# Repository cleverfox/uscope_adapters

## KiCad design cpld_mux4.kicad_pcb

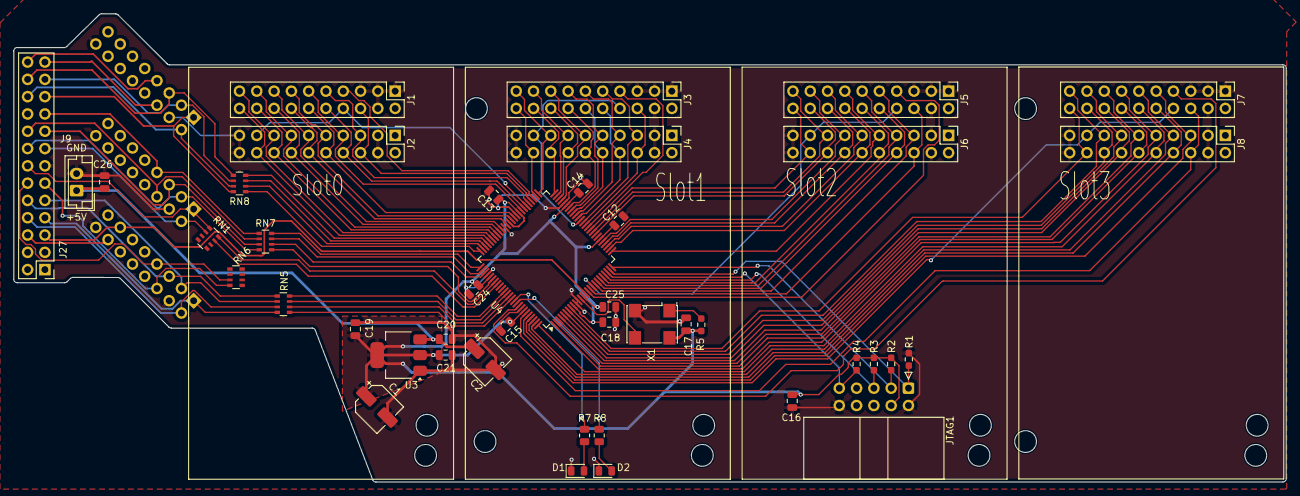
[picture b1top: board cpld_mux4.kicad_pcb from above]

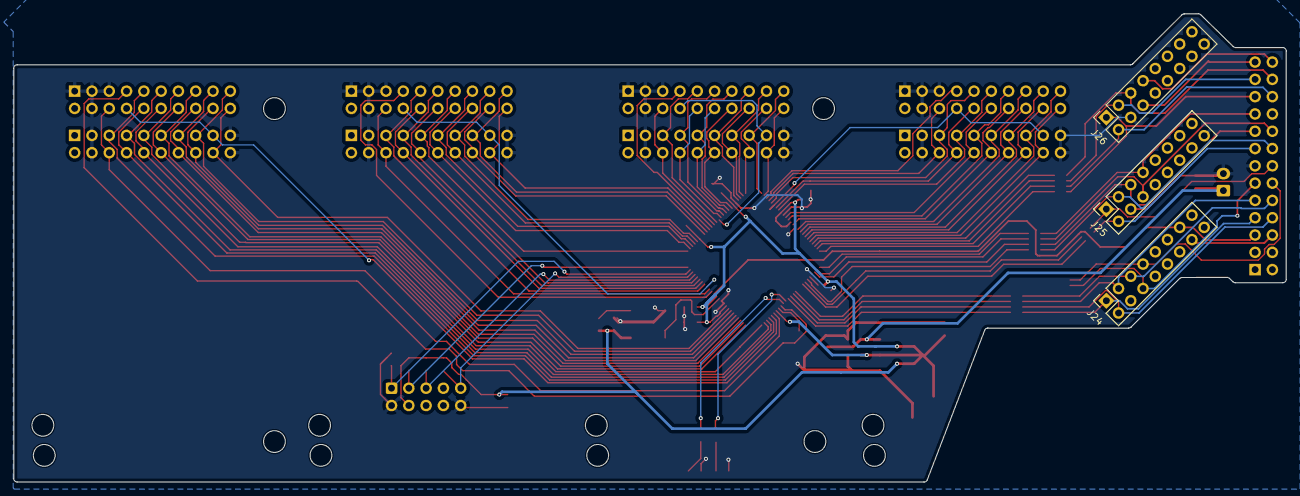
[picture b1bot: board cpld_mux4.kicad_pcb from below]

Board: 2 copper layers, 186.9 x 68.8 mm, 58 parts (3 on the bottom side), 112 nets.

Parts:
C1: 47uF 16V D5xL5.4mm; CP_Elec_5x5.4
C2: 47uF 16V; CP_Elec_5x5.4
C12, C13, C14, C15, C16, C17, C18, C19, C24, C25, C26: 100nF; C_0805_2012Metric
C20, C21: C_Small; C_0805_2012Metric
D1, D2: LED; LED_0805_2012Metric
H1, H3, H5, H7: DAC; MountingHole_3.2mm_M3
H2, H4, H6, H8: ADC; MountingHole_3.2mm_M3
H9, H10, H11, H12: MountingHole; MountingHole_3.2mm_M3
J1, J3, J5, J7: DAC; PinHeader_2x10_P2.54mm_Vertical
J2, J4, J6, J8: ADC; PinHeader_2x10_P2.54mm_Vertical
J9: Conn_01x02_Pin; JST_EH_B2B-EH-A_1x02_P2.50mm_Vertical
J24, J25, J26: Conn_02x08_Odd_Even; PinSocket_2x08_P2.54mm_Vertical
J27: Conn_02x13_Odd_Even; PinHeader_2x13_P2.54mm_Vertical
JTAG1: CONN_02X05; IDC-Header_2x05_P2.54mm_Horizontal
R1, R2, R3, R4: 10K; R_0603_1608Metric_Pad0.98x0.95mm_HandSolder
R5: 0; R_0603_1608Metric_Pad0.98x0.95mm_HandSolder
R7, R8: 1k; R_0805_2012Metric
RN1, RN5, RN6, RN7, RN8: R_Pack04; R_Array_Convex_4x0603
U3: AMS1117-3.3; SOT-223-3_TabPin2
U4: EPM240T100C5N; LQFP-100_14x14mm_P0.5mm
X1: SG-7050CCN; Oscillator_SMD_Abracon_ASV-4Pin_7.0x5.1mm

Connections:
+3V3: C1.1, C12.1, C13.1, C14.1, C15.1, C16.1, C17.1, C18.1, C19.1, C21.1, C24.1, C25.1, JTAG1.4, R2.1, R3.1, R4.1, R5.1, U3.2 (VO), U4.9 (VCCIO1), U4.13 (VCCINT), U4.31 (VCCIO1), U4.45 (VCCIO1), U4.59 (VCCIO2), U4.63 (VCCINT), U4.80 (VCCIO2), U4.94 (VCCIO2), X1.4 (Vdd)
/BA0: RN8.8 (R1.2), U4.72 (IO2_72)
/BA1: RN8.7 (R2.2), U4.73 (IO2_73)
/BA2: RN8.6 (R3.2), U4.74 (IO2_74)
/BA3: RN8.5 (R4.2), U4.75 (IO2_75)
/BA4: RN7.8 (R1.2), U4.76 (IO2_76)
/BA5: RN7.7 (R2.2), U4.77 (IO2_77)
/BA6: RN7.6 (R3.2), U4.78 (IO2_78)
/BA7: RN7.5 (R4.2), U4.81 (IO2_81)
/BA8: RN1.8 (R1.2), U4.82 (IO2_82)
/BA9: RN1.7 (R2.2), U4.83 (IO2_83)
/BA10: RN6.6 (R3.2), U4.84 (IO2_84)
/BA11: RN6.5 (R4.2), U4.85 (IO2_85)
/BA12: RN5.8 (R1.2), U4.86 (IO2_86)
/BA13: RN5.7 (R2.2), U4.87 (IO2_87)
/BA14: RN5.6 (R3.2), U4.88 (IO2_88)
/BA15: RN5.5 (R4.2), U4.89 (IO2_89)
/CM_CLK_M3: J24.13, J27.5, U4.14 (IO1_14/GCLK1)
/CM_STB_N1: J24.14, J27.6
/D1_1: J24.1, J27.7, RN5.4 (R4.1)
/D1_2: J24.2, J27.8, RN5.3 (R3.1)
/D1_3: J24.3, J27.9, RN5.2 (R2.1)
/D1_4: J24.5, J27.10, RN5.1 (R1.1)
/D1_5: J24.6, J27.11, RN6.4 (R4.1)
/D1_6: J24.7, J27.12, RN6.3 (R3.1)
/D2_1: J25.1, J27.14, RN1.1 (R1.1)
/D2_2: J25.2, J27.15, RN1.2 (R2.1)
/D2_3: J25.3, J27.16, RN7.4 (R4.1)
/D2_4: J25.5, J27.17, RN7.3 (R3.1)
/D2_5: J25.6, J27.18, RN7.2 (R2.1)
/D2_6: J25.7, J27.19, RN7.1 (R1.1)
/D3_1: J26.1, J27.21, RN8.4 (R4.1)
/D3_2: J26.2, J27.22, RN8.3 (R3.1)
/D3_3: J26.3, J27.23, RN8.2 (R2.1)
/D3_4: J26.5, J27.24, RN8.1 (R1.1)
/D3_5: J26.6, J27.25
/D3_6: J26.7, J27.26
/LD0: D2.2 (A), R8.2
/LD1: D1.2 (A), R7.2
/LED0: R8.1, U4.91 (IO2_91)
/LED1: R7.1, U4.90 (IO2_90)
/S1D0: J3.20, J4.18, U4.52 (IO2_52)
/S3C: J7.6, J8.6, U4.95 (IO2_95)
/S3D7: J7.13, J8.9, U4.1 (IO2_1)
/S3D8: J7.12, J8.10, U4.100 (IO2_100)
/S3D9: J7.11, J8.7, U4.99 (IO2_99)
/S3D10: J7.10, J8.8, U4.98 (IO2_98)
/S3D11: J7.9, J8.5, U4.97 (IO2_97)
/S3D12: J7.8, J8.17, U4.96 (IO2_96)
/S3D13: J7.7, U4.92 (IO2_92)
/TCK: JTAG1.1, R1.2, U4.24 (TCK)
/TDI: JTAG1.9, R4.2, U4.23 (TDI)
/TDO: JTAG1.3, R2.2, U4.25 (TDO)
/TMS: JTAG1.5, R3.2, U4.22 (TMS)
/VCC_5V: C2.1, C20.1, C26.1, J9.1, U3.3 (VI)
/XTALCLK: U4.12 (IO1_12/GCLK0), X1.3 (OUT)
/ad_da_socket1/CLK: J3.6, J4.6, U4.37 (IO1_37)
/ad_da_socket1/D1: J3.19, J4.15, U4.51 (IO1_51)
/ad_da_socket1/D2: J3.18, J4.16, U4.50 (IO1_50)
/ad_da_socket1/D3: J3.17, J4.13, U4.49 (IO1_49)
/ad_da_socket1/D4: J3.16, J4.14, U4.48 (IO1_48)
/ad_da_socket1/D5: J3.15, J4.11, U4.47 (IO1_47)
/ad_da_socket1/D6: J3.14, J4.12, U4.44 (IO1_44/DEV_CLRn)
/ad_da_socket1/D7: J3.13, J4.9, U4.43 (IO1_43/DEV_OE)
/ad_da_socket1/D8: J3.12, J4.10, U4.42 (IO1_42)
/ad_da_socket1/D9: J3.11, J4.7, U4.41 (IO1_41)
/ad_da_socket1/D10: J3.10, J4.8, U4.40 (IO1_40)
/ad_da_socket1/D11: J3.9, J4.5, U4.38 (IO1_38)
/ad_da_socket1/D12: J3.8, J4.17, U4.39 (IO1_39)
/ad_da_socket1/D13: J3.7, U4.36 (IO1_36)
/ad_da_socket1/VCC_5V: J3.2, J4.1, J4.2
/ad_da_socket2/CLK: J5.6, J6.6, U4.16 (IO1_16)
/ad_da_socket2/D0: J5.20, J6.18, U4.35 (IO1_35)
/ad_da_socket2/D1: J5.19, J6.15, U4.34 (IO1_34)
/ad_da_socket2/D2: J5.18, J6.16, U4.33 (IO1_33)
/ad_da_socket2/D3: J5.17, J6.13, U4.30 (IO1_30)
/ad_da_socket2/D4: J5.16, J6.14, U4.29 (IO1_29)
/ad_da_socket2/D5: J5.15, J6.11, U4.28 (IO1_28)
/ad_da_socket2/D6: J5.14, J6.12, U4.27 (IO1_27)
/ad_da_socket2/D7: J5.13, J6.9, U4.26 (IO1_26)
/ad_da_socket2/D8: J5.12, J6.10, U4.21 (IO1_21)
/ad_da_socket2/D9: J5.11, J6.7, U4.20 (IO1_20)
/ad_da_socket2/D10: J5.10, J6.8, U4.19 (IO1_19)
/ad_da_socket2/D11: J5.9, J6.5, U4.18 (IO1_18)
/ad_da_socket2/D12: J5.8, J6.17, U4.17 (IO1_17)
/ad_da_socket2/D13: J5.7, U4.15 (IO1_15)
/ad_da_socket2/VCC_5V: J5.2, J6.1, J6.2
/ad_da_socket3/D0: J7.20, J8.18, U4.8 (IO1_8)
/ad_da_socket3/D1: J7.19, J8.15, U4.7 (IO1_7)
/ad_da_socket3/D2: J7.18, J8.16, U4.6 (IO1_6)
/ad_da_socket3/D3: J7.17, J8.13, U4.5 (IO1_5)
/ad_da_socket3/D4: J7.16, J8.14, U4.4 (IO1_4)
/ad_da_socket3/D5: J7.15, J8.11, U4.3 (IO1_3)
/ad_da_socket3/D6: J7.14, J8.12, U4.2 (IO1_2)
/ad_da_socket3/VCC_5V: J7.2, J8.1, J8.2
/ad_da_socket/CLK: J1.6, J2.6, U4.54 (IO2_54)
/ad_da_socket/D0: J1.20, J2.18, U4.71 (IO2_71)
/ad_da_socket/D1: J1.19, J2.15, U4.70 (IO2_70)
/ad_da_socket/D2: J1.18, J2.16, U4.69 (IO2_69)
/ad_da_socket/D3: J1.17, J2.13, U4.68 (IO2_68)
/ad_da_socket/D4: J1.16, J2.14, U4.67 (IO2_67)
/ad_da_socket/D5: J1.15, J2.11, U4.66 (IO2_66)
/ad_da_socket/D6: J1.14, J2.12, U4.64 (IO2_64/GCLK3)
/ad_da_socket/D7: J1.13, J2.9, U4.62 (IO2_62/GCLK2)
/ad_da_socket/D8: J1.12, J2.10, U4.61 (IO2_61)
/ad_da_socket/D9: J1.11, J2.7, U4.58 (IO2_58)
/ad_da_socket/D10: J1.10, J2.8, U4.57 (IO2_57)
/ad_da_socket/D11: J1.9, J2.5, U4.55 (IO2_55)
/ad_da_socket/D12: J1.8, J2.17, U4.56 (IO2_56)
/ad_da_socket/D13: J1.7, U4.53 (IO2_53)
/ad_da_socket/VCC_5V: J1.2, J2.1, J2.2
GND: C1.2, C2.2, C12.2, C13.2, C14.2, C15.2, C16.2, C17.2, C18.2, C19.2, C20.2, C21.2, C24.2, C25.2, C26.2, D1.1 (K), D2.1 (K), J1.1, J1.3, J1.4, J1.5, J2.3, J2.4, J2.19, J2.20, J3.1, J3.3, J3.4, J3.5, J4.3, J4.4, J4.19, J4.20, J5.1, J5.3, J5.4, J5.5, J6.3, J6.4, J6.19, J6.20, J7.1, J7.3, J7.4, J7.5, J8.3, J8.4, J8.19, J8.20, J9.2, J24.4, J24.16, J25.4, J25.16, J26.4, J26.16, J27.13, J27.20, JTAG1.2, JTAG1.10, R1.1, U3.1 (GND), U4.10 (GNDIO), U4.11 (GNDINT), U4.32 (GNDIO), U4.46 (GNDIO), U4.60 (GNDIO), U4.65 (GNDINT), U4.79 (GNDIO), U4.93 (GNDIO), X1.2 (GND)

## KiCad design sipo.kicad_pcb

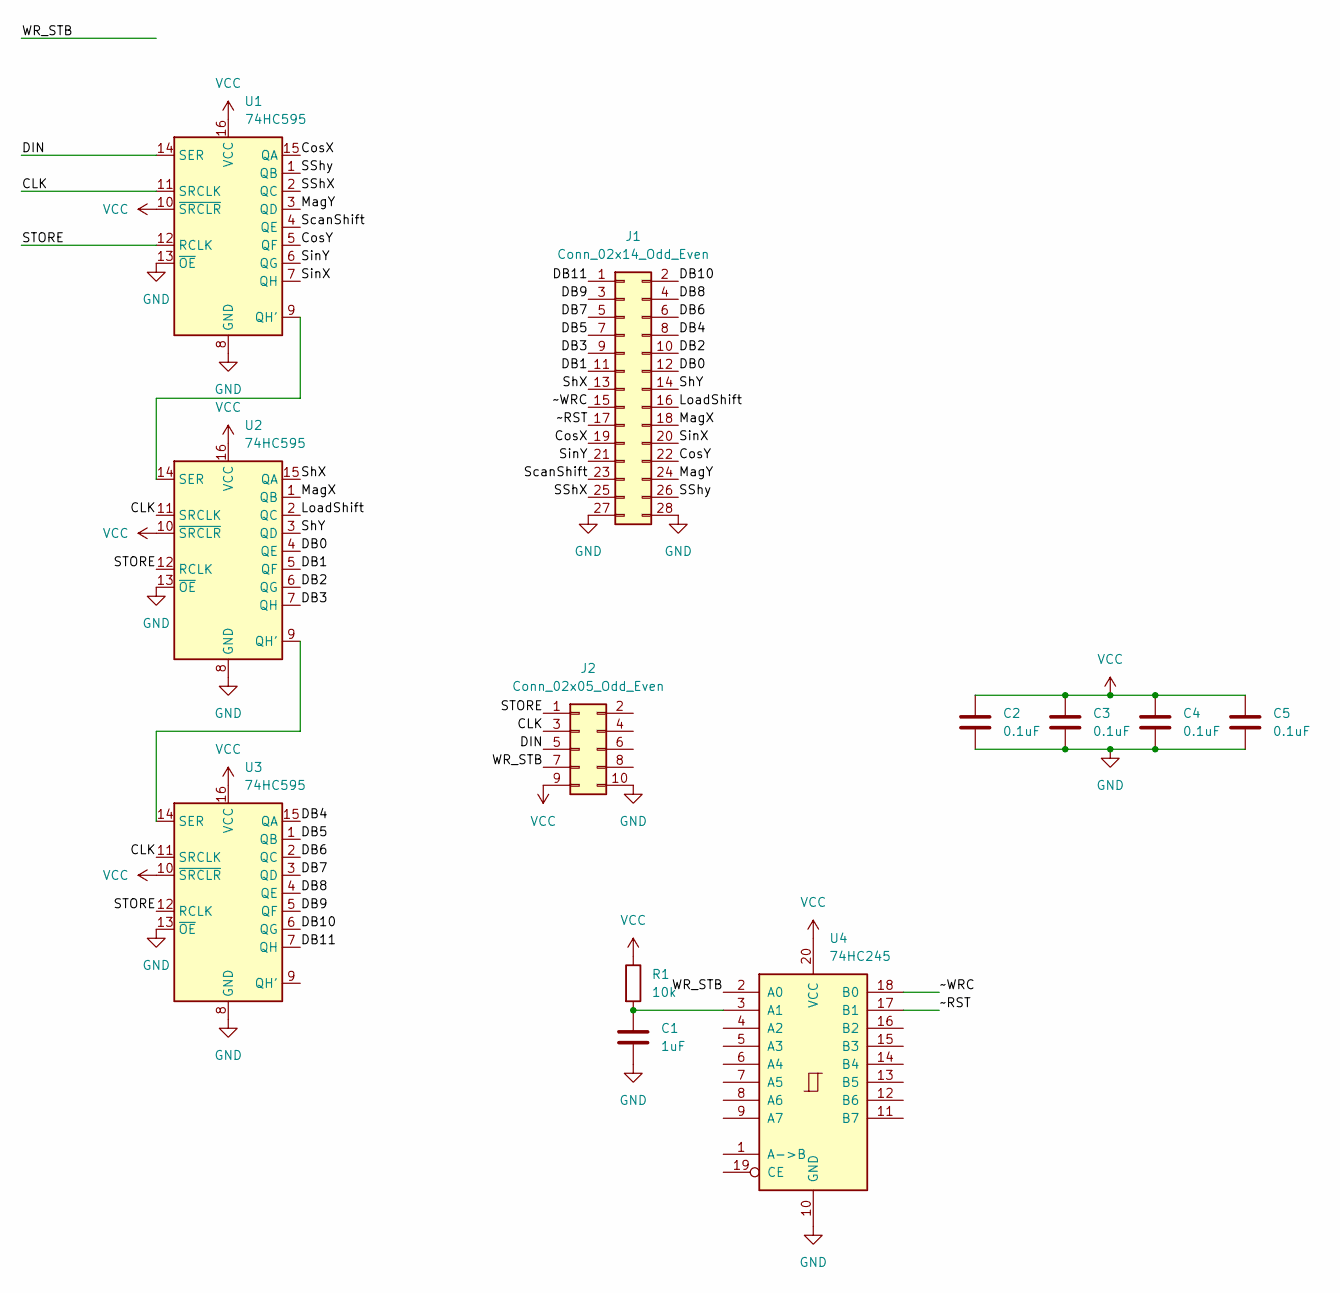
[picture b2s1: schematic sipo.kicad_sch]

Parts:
C1: 1uF; C_0805_2012Metric
C2, C3, C4, C5: 0.1uF; C_0603_1608Metric
J1: Conn_02x14_Odd_Even; PinSocket_2x14_P2.00mm_Vertical
J2: Conn_02x05_Odd_Even; PinHeader_2x05_P2.54mm_Vertical
R1: 10k; R_0603_1608Metric
U1, U2, U3: 74HC595; SOIC-16_3.9x9.9mm_P1.27mm
U4: 74HC245; TSSOP-20_4.4x6.5mm_P0.65mm

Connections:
/CLK: J2.3, U1.11 (SRCLK), U2.11 (SRCLK), U3.11 (SRCLK)
/CosX: J1.19, U1.15 (QA)
/CosY: J1.22, U1.5 (QF)
/DB0: J1.12, U2.4 (QE)
/DB1: J1.11, U2.5 (QF)
/DB2: J1.10, U2.6 (QG)
/DB3: J1.9, U2.7 (QH)
/DB4: J1.8, U3.15 (QA)
/DB5: J1.7, U3.1 (QB)
/DB6: J1.6, U3.2 (QC)
/DB7: J1.5, U3.3 (QD)
/DB8: J1.4, U3.4 (QE)
/DB9: J1.3, U3.5 (QF)
/DB10: J1.2, U3.6 (QG)
/DB11: J1.1, U3.7 (QH)
/DIN: J2.5, U1.14 (SER)
/LoadShift: J1.16, U2.2 (QC)
/MagX: J1.18, U2.1 (QB)
/MagY: J1.24, U1.3 (QD)
/SShX: J1.25, U1.2 (QC)
/SShy: J1.26, U1.1 (QB)
/STORE: J2.1, U1.12 (RCLK), U2.12 (RCLK), U3.12 (RCLK)
/ScanShift: J1.23, U1.4 (QE)
/ShX: J1.13, U2.15 (QA)
/ShY: J1.14, U2.3 (QD)
/SinX: J1.20, U1.7 (QH)
/SinY: J1.21, U1.6 (QG)
/WR_STB: J2.7, U4.2 (A0)
/~RST: J1.17, U4.17 (B1)
/~WRC: J1.15, U4.18 (B0)
GND: C1.2, C2.2, C3.2, C4.2, C5.2, J1.27, J1.28, J2.10, U1.8 (GND), U1.13 (~OE), U2.8 (GND), U2.13 (~OE), U3.8 (GND), U3.13 (~OE), U4.10 (GND)
unnamed: U1.9 (QH'), U2.14 (SER)
unnamed: U2.9 (QH'), U3.14 (SER)
unnamed: C1.1, R1.2, U4.3 (A1)
VCC: C2.1, C3.1, C4.1, C5.1, J2.9, R1.1, U1.10 (~SRCLR), U1.16 (VCC), U2.10 (~SRCLR), U2.16 (VCC), U3.10 (~SRCLR), U3.16 (VCC), U4.20 (VCC)

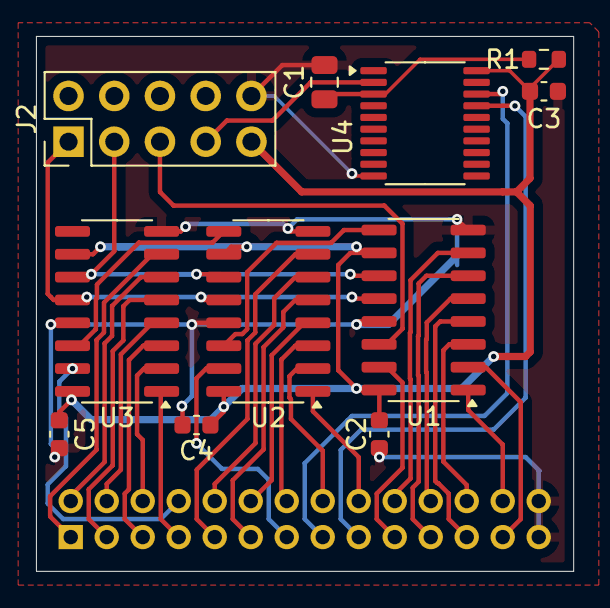
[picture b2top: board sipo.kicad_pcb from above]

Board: 2 copper layers, 29.8 x 29.7 mm, 12 parts (1 on the bottom side), 35 nets.

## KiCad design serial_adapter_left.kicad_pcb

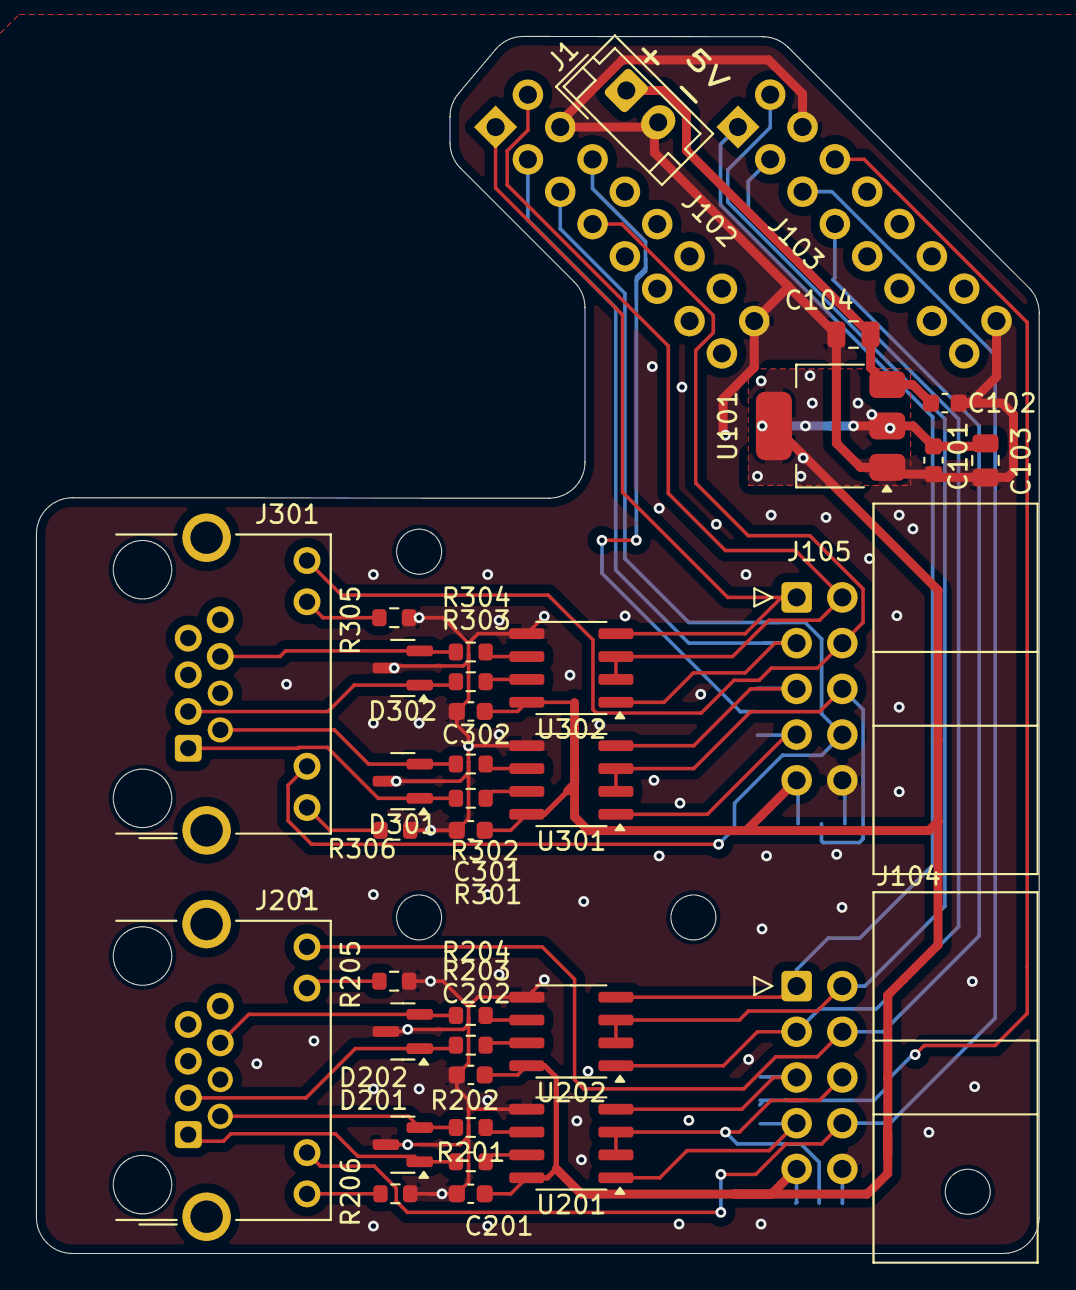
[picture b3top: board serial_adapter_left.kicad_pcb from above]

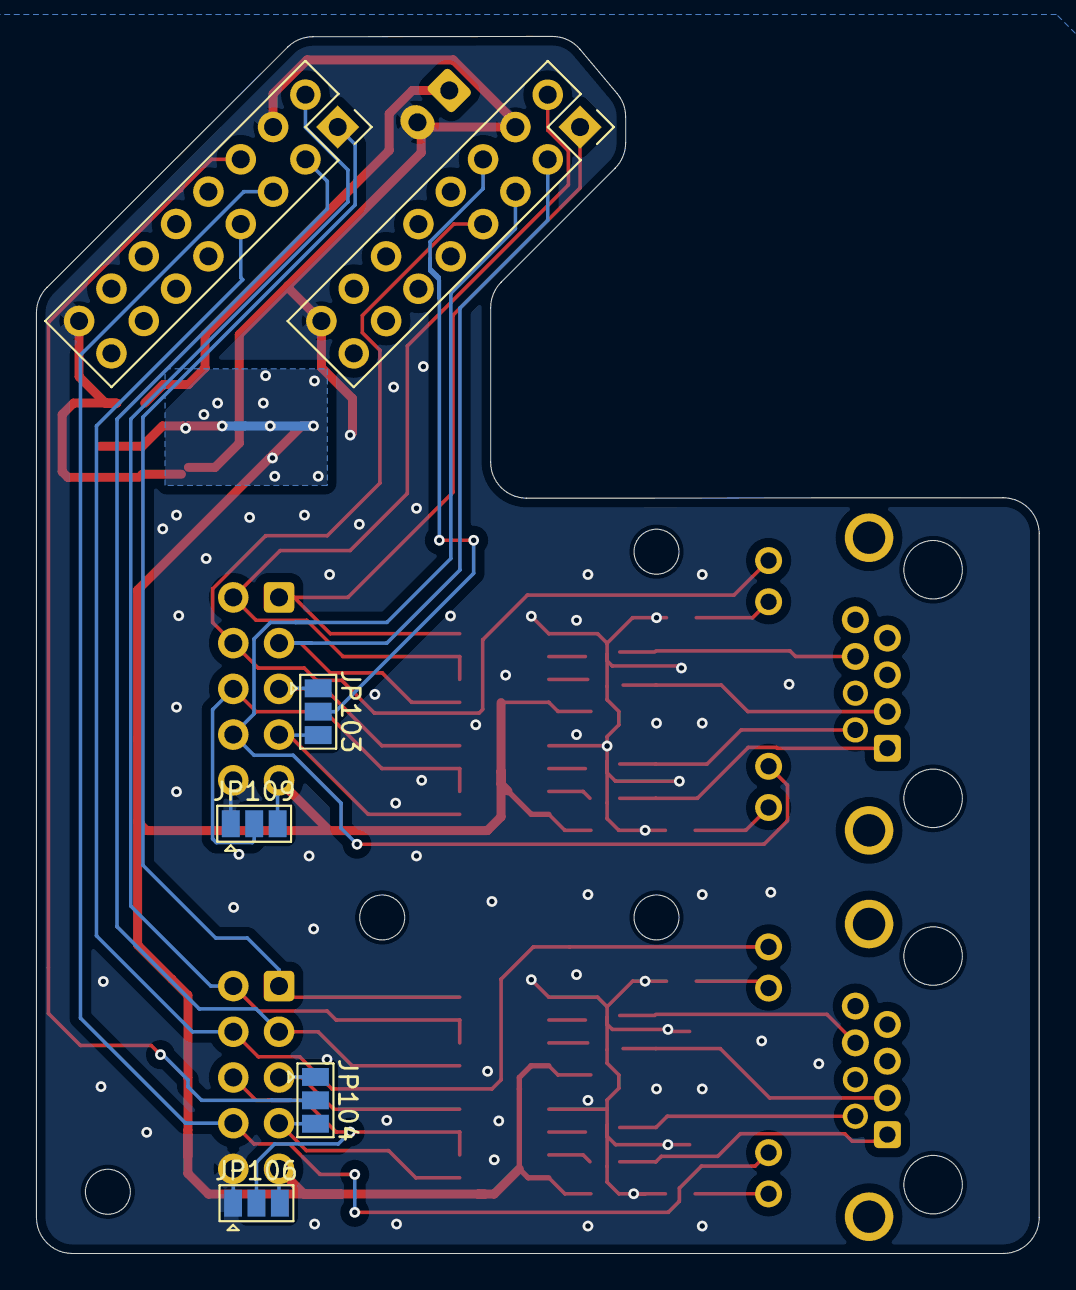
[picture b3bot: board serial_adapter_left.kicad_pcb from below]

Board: 2 copper layers, 55.7 x 67.6 mm, 44 parts (6 on the bottom side), 41 nets.

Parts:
C101, C102, C201, C202, C301, C302: 100nF; C_0603_1608Metric
C103, C104: 4.7uF; C_0805_2012Metric
D201, D202, D301, D302: CDSOT23-SM712; SOT-23
H101, H102, H103, H104: MountingHole; MountingHole_2.5mm
J1: Conn_01x02_Pin; JST_EH_B2B-EH-A_1x02_P2.50mm_Vertical
J102, J103: Conn_02x08_Odd_Even; PinSocket_2x08_P2.54mm_Vertical
J104, J105: Conn_01x08; IDC-Header_2x05_P2.54mm_Horizontal
J201, J301: DS1128-09-S8B8S; RJ45_Connfly_DS1128-09-S8xx-S_Horizontal
JP103, JP104, JP106, JP109: Jumper_3_Open; SolderJumper-3_P1.3mm_Open_Pad1.0x1.5mm
R201, R202, R203, R204, R301, R302, R303, R304: 10; R_0603_1608Metric
R205, R206, R305, R306: 1k; R_0603_1608Metric
U101: LM317_SOT-223; SOT-223-3_TabPin2
U201, U202, U301, U302: THVD1450DR; SOIC-8_3.9x4.9mm_P1.27mm

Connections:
+3V3: C101.2, C103.1, C201.2, C202.2, C301.2, C302.2, J104.9, J105.9, JP106.3 (B), JP109.3 (B), U101.2 (VO), U201.8 (VCC), U202.8 (VCC), U301.8 (VCC), U302.8 (VCC)
/D1_5: J102.6, JP103.2 (C)
/D2_5: J103.6, JP104.2 (C)
/I0L1: J103.7, J104.4, J201.12
/I0L2: J103.5, J104.8, J201.10
/I0U1DIR: J103.2, J104.2, U202.2 (~RE), U202.3 (DE)
/I0U1RX: J103.3, J104.3, U202.1 (R)
/I0U1TX: J103.1, J104.1, U202.4 (D)
/I0U2DIR: J104.6, JP106.2 (C), U201.2 (~RE), U201.3 (DE)
/I0U2RX: J104.7, JP104.3 (B), U201.1 (R)
/I0U2TX: J104.5, JP104.1 (A), U201.4 (D)
/I1I1DIR: J102.2, J105.2, U302.2 (~RE), U302.3 (DE)
/I1L1: J102.7, J105.4, J301.12
/I1L2: J102.5, J105.8, J301.10
/I1U1RX: J102.3, J105.3, U302.1 (R)
/I1U1TX: J102.1, J105.1, U302.4 (D)
/I2DIR: J105.6, JP109.2 (C), U301.2 (~RE), U301.3 (DE)
/I2U2RX: J105.7, JP103.3 (B), U301.1 (R)
/I2U2TX: J105.5, JP103.1 (A), U301.4 (D)
/VCC_5V: C102.1, C104.1, J1.1, U101.3 (VI)
GND: C101.1, C102.2, C103.2, C104.2, C201.1, C202.1, C301.1, C302.1, D201.3 (common), D202.3 (common), D301.3 (common), D302.3 (common), J1.2, J102.4, J102.16, J103.4, J103.16, J104.10, J105.10, JP106.1 (A), JP109.1 (A), R205.1, R206.1, R305.1, R306.1, U101.1 (ADJ), U201.5 (GND), U202.5 (GND), U301.5 (GND), U302.5 (GND)
unnamed: D201.1 (A1), J201.1, R201.2
unnamed: D201.2 (A2), J201.2, R202.2
unnamed: D202.1 (A1), J201.3, R203.1
unnamed: D202.2 (A2), J201.6, R204.1
unnamed: D301.1 (A1), J301.1, R301.2
unnamed: D301.2 (A2), J301.2, R302.2
unnamed: D302.1 (A1), J301.3, R303.1
unnamed: D302.2 (A2), J301.6, R304.1
unnamed: J201.9, R206.2
unnamed: J201.11, R205.2
unnamed: J301.9, R306.2
unnamed: J301.11, R305.2
unnamed: R202.1, U201.6 (A)
unnamed: R201.1, U201.7 (B)
unnamed: R204.2, U202.6 (A)
unnamed: R203.2, U202.7 (B)
unnamed: R302.1, U301.6 (A)
unnamed: R301.1, U301.7 (B)
unnamed: R304.2, U302.6 (A)
unnamed: R303.2, U302.7 (B)

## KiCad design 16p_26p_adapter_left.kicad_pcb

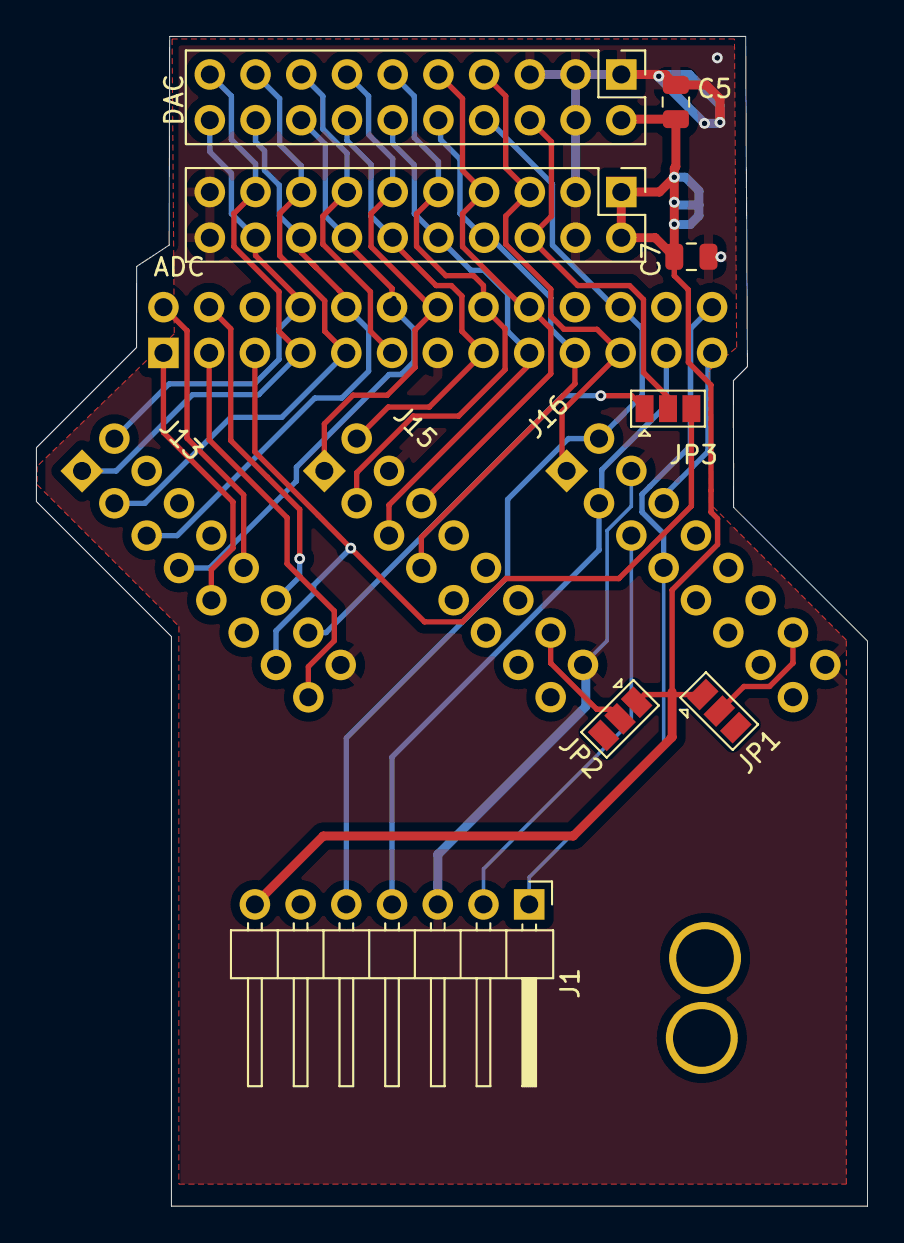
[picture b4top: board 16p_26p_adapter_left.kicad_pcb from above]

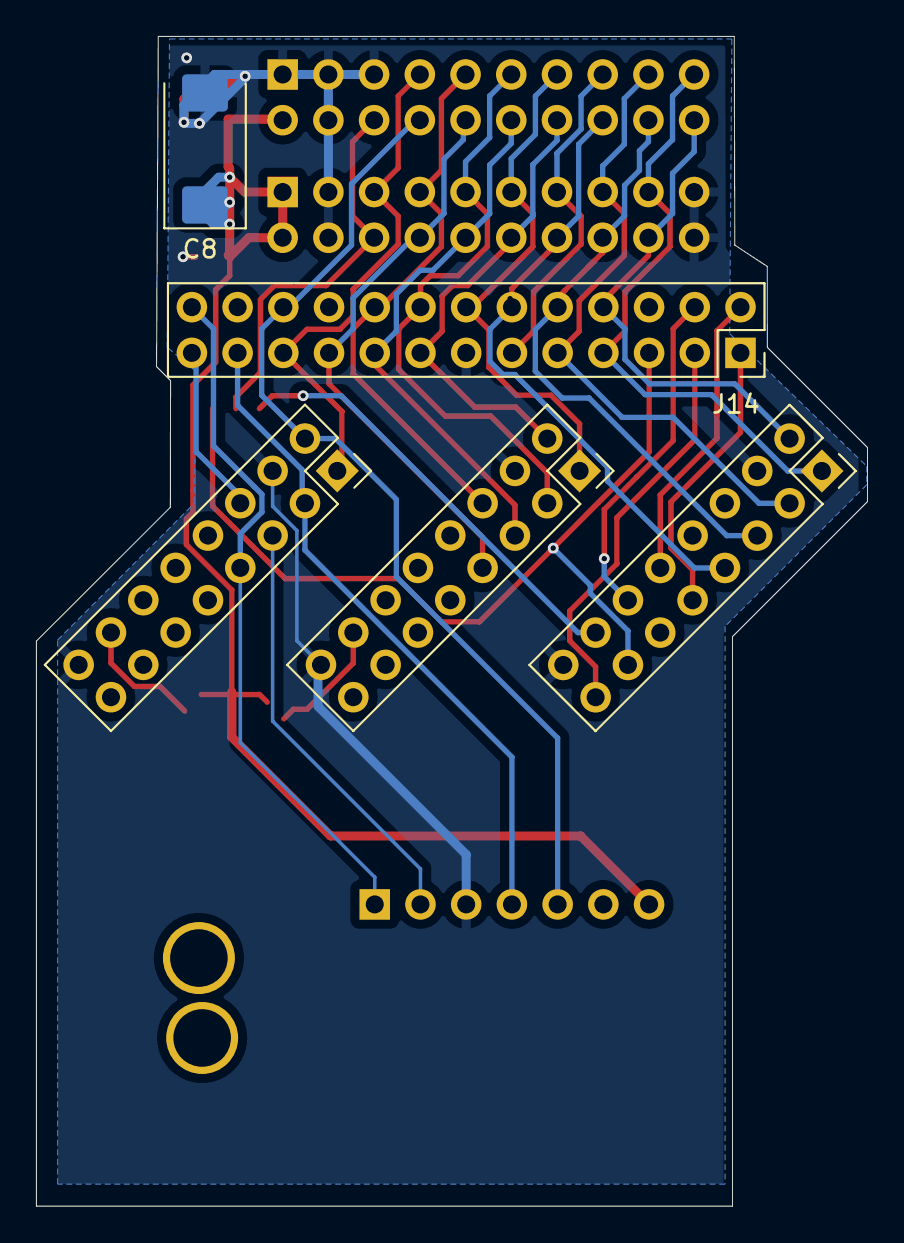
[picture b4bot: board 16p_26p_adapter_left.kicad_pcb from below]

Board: 2 copper layers, 46.2 x 65.0 mm, 15 parts (4 on the bottom side), 29 nets.

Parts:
C5, C7: 100nF; C_0805_2012Metric
C8: 10v47uF; CP_EIA-7343-40_Kemet-Y
H6: DAC; MountingHole_3.5mm_Pad_Via
H10: ADC; MountingHole_3.5mm_Pad_Via
J1: Conn_01x07; PinHeader_1x07_P2.54mm_Horizontal
J13, J15, J16: Conn_02x08_Odd_Even; PinSocket_2x08_P2.54mm_Vertical
J14: Conn_02x13_Odd_Even; PinHeader_2x13_P2.54mm_Vertical
J18: DAC; PinHeader_2x10_P2.54mm_Vertical
J19: ADC; PinHeader_2x10_P2.54mm_Vertical
JP1, JP2: Jumper_2_Open; SolderJumper-3_P1.3mm_Open_Pad1.0x1.5mm
JP3: Jumper_3_Open; SolderJumper-3_P1.3mm_Open_Pad1.0x1.5mm

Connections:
/CM_A_N5: J13.9, J14.1
/CM_B_N3: J13.10, J14.2
/CM_CLK_M3: J13.13, J14.5, JP3.3 (B)
/CM_D_P4: J13.12, J14.4
/CM_OE_M4: J13.15, J14.3
/CM_STB_N1: J13.14, J14.6, JP3.1 (A)
/D1_1: J13.1, J14.7, J18.19, J19.17
/D1_2: J13.2, J14.8, J18.20, J19.18
/D1_3: J13.3, J14.9, J18.17, J19.15
/D1_4: J13.5, J14.10, J18.18, J19.16
/D1_5: J13.6, J14.11, J18.15, J19.13
/D1_6: J13.7, J14.12, J18.16, J19.14
/D2_1: J14.14, J15.1, J18.13, J19.11
/D2_2: J14.15, J15.2, J18.14, J19.12
/D2_3: J14.16, J15.3, J18.11, J19.9
/D2_4: J14.17, J15.5, J18.12, J19.10
/D2_5: J14.18, J15.6, J18.9, J19.7
/D2_6: J14.19, J15.7, J18.10, J19.8
/D3_1: J14.21, J16.1, J18.7, J19.5
/D3_2: J1.5, J14.22, J16.2, J18.8
/D3_3: J1.4, J14.23, J16.3
/D3_4: J1.2, J14.24, J16.5
/D3_5: J14.25, J16.6
/D3_6: J1.1, J14.26, J16.7
/VCC_5V: C5.1, C7.1, C8.1, J1.7, J18.2, J19.1, J19.2, JP1.1 (A), JP2.1 (A)
/VCC_J15: J15.14, JP2.2 (B)
/VCC_J16: J16.14, JP1.2 (B)
GND: C5.2, C7.2, C8.2, J1.3, J13.4, J13.16, J14.13, J14.20, J15.4, J15.16, J16.4, J16.16, J18.1, J18.3, J18.4, J18.5, J19.3, J19.4, J19.19, J19.20
unnamed: J18.6, J19.6, JP3.2 (C)

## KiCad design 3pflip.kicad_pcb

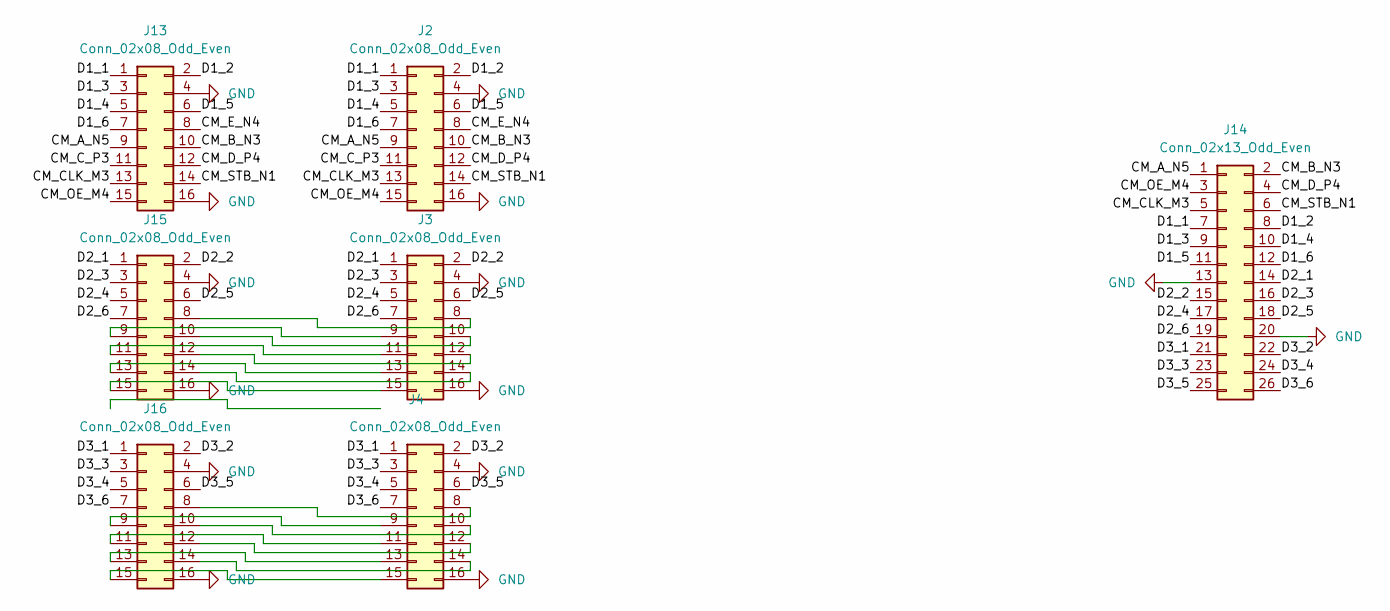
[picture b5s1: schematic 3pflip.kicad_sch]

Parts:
J2, J3, J4: Conn_02x08_Odd_Even; PinHeader_2x08_P2.54mm_Vertical_SMD
J13, J15, J16: Conn_02x08_Odd_Even; PinSocket_2x08_P2.54mm_Vertical_SMD
J14: Conn_02x13_Odd_Even; PinHeader_2x13_P2.54mm_Vertical

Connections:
/CM_A_N5: J2.9, J13.9, J14.1
/CM_B_N3: J2.10, J13.10, J14.2
/CM_CLK_M3: J2.13, J13.13, J14.5
/CM_C_P3: J2.11, J13.11
/CM_D_P4: J2.12, J13.12, J14.4
/CM_E_N4: J2.8, J13.8
/CM_OE_M4: J2.15, J13.15, J14.3
/CM_STB_N1: J2.14, J13.14, J14.6
/D1_1: J2.1, J13.1, J14.7
/D1_2: J2.2, J13.2, J14.8
/D1_3: J2.3, J13.3, J14.9
/D1_4: J2.5, J13.5, J14.10
/D1_5: J2.6, J13.6, J14.11
/D1_6: J2.7, J13.7, J14.12
/D2_1: J3.1, J14.14, J15.1
/D2_2: J3.2, J14.15, J15.2
/D2_3: J3.3, J14.16, J15.3
/D2_4: J3.5, J14.17, J15.5
/D2_5: J3.6, J14.18, J15.6
/D2_6: J3.7, J14.19, J15.7
/D3_1: J4.1, J14.21, J16.1
/D3_2: J4.2, J14.22, J16.2
/D3_3: J4.3, J14.23, J16.3
/D3_4: J4.5, J14.24, J16.5
/D3_5: J4.6, J14.25, J16.6
/D3_6: J4.7, J14.26, J16.7
GND: J2.4, J2.16, J3.4, J3.16, J4.4, J4.16, J13.4, J13.16, J14.13, J14.20, J15.4, J15.16, J16.4, J16.16
unnamed: J3.8, J15.8
unnamed: J3.9, J15.9
unnamed: J3.10, J15.10
unnamed: J3.11, J15.11
unnamed: J3.12, J15.12
unnamed: J3.13, J15.13
unnamed: J3.14, J15.14
unnamed: J3.15, J15.15
unnamed: J4.8, J16.8
unnamed: J4.9, J16.9
unnamed: J4.10, J16.10
unnamed: J4.11, J16.11
unnamed: J4.12, J16.12
unnamed: J4.13, J16.13
unnamed: J4.14, J16.14
unnamed: J4.15, J16.15

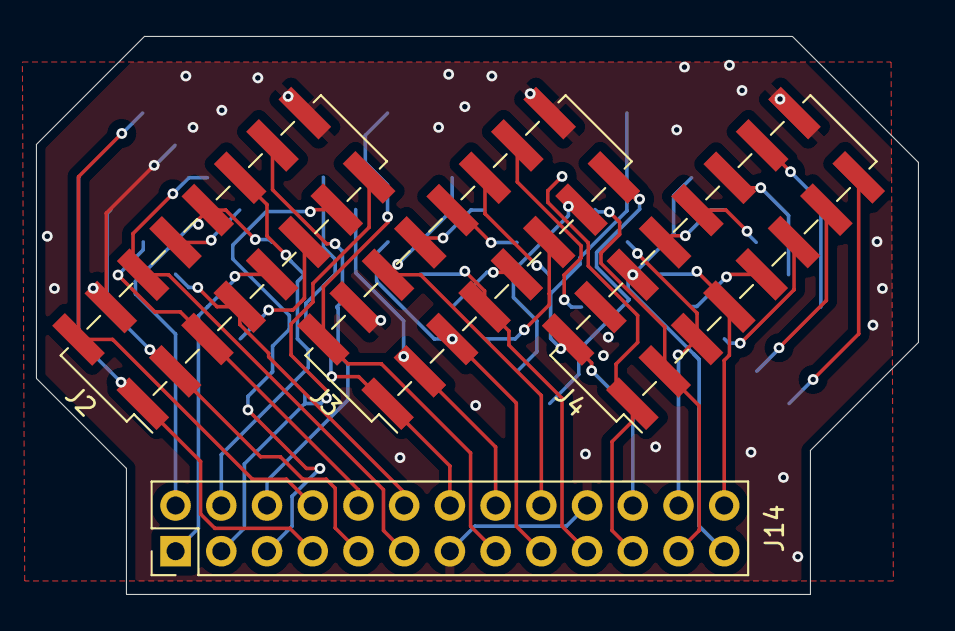
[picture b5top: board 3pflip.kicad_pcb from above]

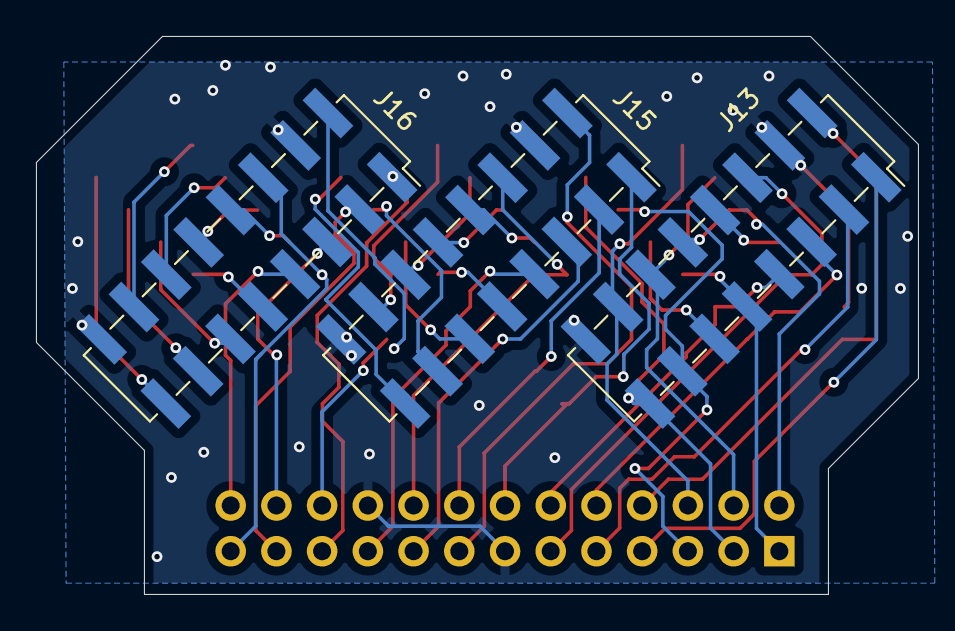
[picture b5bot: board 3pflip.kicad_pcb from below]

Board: 2 copper layers, 49.0 x 31.0 mm, 7 parts (3 on the bottom side), 43 nets.
